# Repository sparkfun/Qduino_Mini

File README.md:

***NOTE:*** *This product was a Kickstarter product. If you are looking for more up-to-date info and the current version of this board, please check out the [current (Storefront) version](https://github.com/sparkfun/Qduino_Mini_SFE), [Qduino Mini product page](https://www.sparkfun.com/products/13614), or the [Arduino board support and library](https://github.com/sparkfun/Arduino_Boards).*

The Qduino Mini is *perfect* to embed in your electronics projects, it's super small, inexpensive, has a battery connector & charger built-in, & a fuel gauge that can tell you when to charge the battery!

The **Qduino Mini is Arduino-compatible & 100% open source, hardware and software** meaning that making and programming your first circuit is a breeze.  Hardware is hard, so we decided to make it a little bit easier.  All of the design files, including EAGLE board files, schematic, and code have been released under an open source license.  Here's what it includes:

* **Battery Charger Circuit** - just plug in USB and it charges the battery with the auto switching circuit - there's no extra charger needed & no digging the battery out of your project so you can charge & program at the same time over USB!
* **Battery Fuel Gauge** - guessing on when your project runs out of juice?  We've got you covered - we have a simple monitor library for your battery so you can remind yourself when it needs a little extra juice.
* **Ultra small, Ultra thin, Ultra light** - The Qduino Mini itself is 0.8in x 1.5in (2cm x 3.9cm) & 0.18oz (5 grams), perfect for quadcopters, drones or high altitude balloon projects.  Both the Qduino Mini and the batteries (LiPos) used to power the board fit are super compact & thin, just right for embedding in your projects.

######Tech Specs:

* **ATmega32U4 Processor** - Arduino Leonardo Compatible
* 32KB Flash Storage
* 2.5KB SRAM
* 1KB EEPROM
* 3.3V @ 8MHz
* 20 Digital I/O // 14 Dedicated
* 12 Analog Channels // 6 Dedicated
* 7 Digital I/O also PWM channels
* SPI, I2C, UART available
* Two RGB LEDs built-in - one for: Charge Status, TX, RX, and the * other user programmable
* **TPS78233** 3.3V 150mA Regulator
* **MCP73832** LiPo Battery Charger
* **MAX17048** LiPo Battery Fuel Gauge

The Qduino Mini is 100% made in the USA! Every board is made and quality tested at SparkFun Electronics, in Niwot, CO.

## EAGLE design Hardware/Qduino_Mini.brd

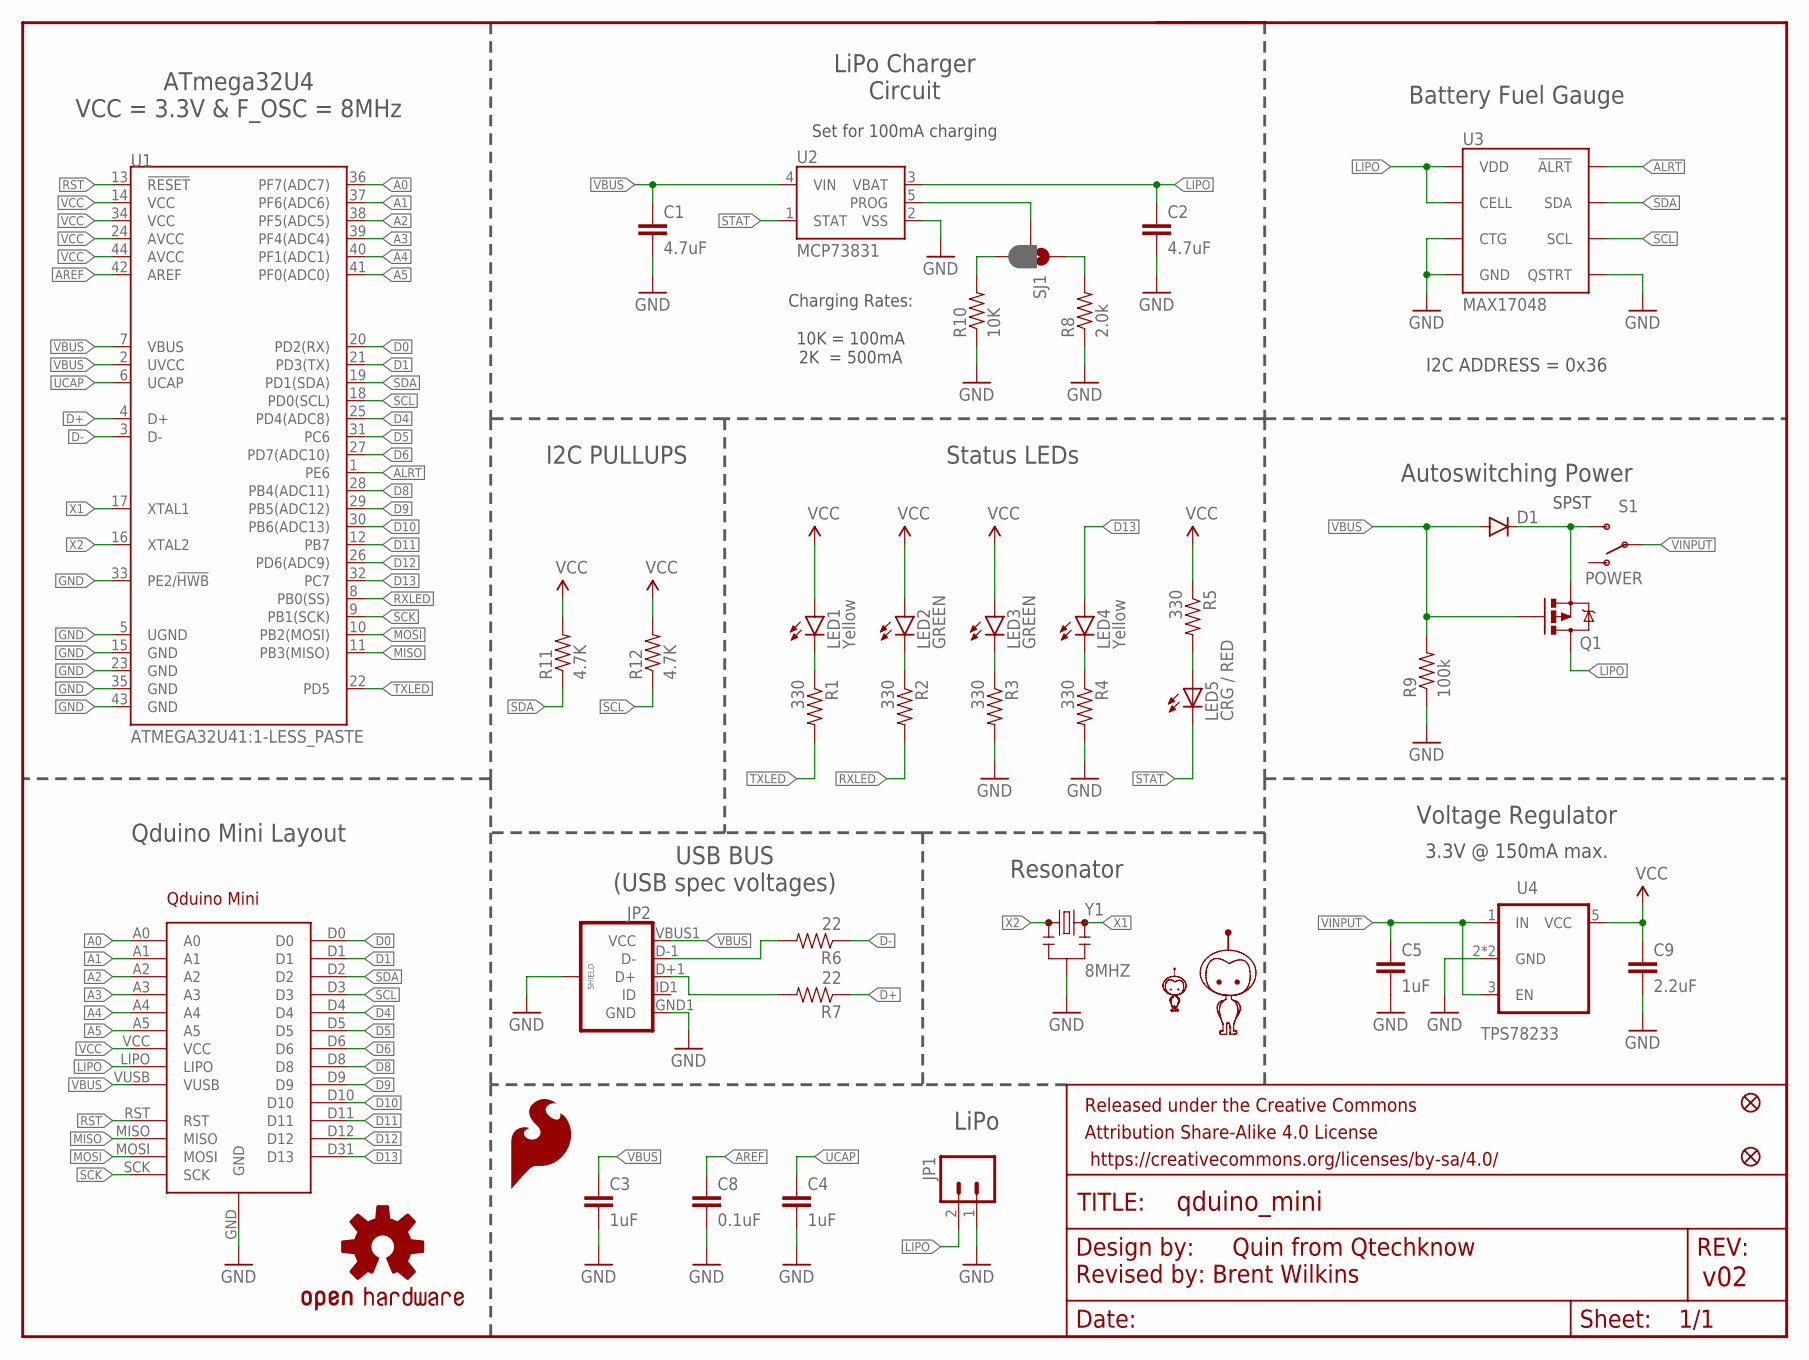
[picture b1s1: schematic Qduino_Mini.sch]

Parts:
C1, C2: 4.7uF; 0603-CAP
C3, C4, C5: 1uF; 0603-CAP
C8: 0.1uF; 0603-CAP
C9: 2.2uF; 0603-CAP
D1: 250mA/100V; SOD-323
FID5, FID6: FIDUCIAL1X2; FIDUCIAL-1X2
FRAME2: FRAME-LETTER; CREATIVE_COMMONS
JP1: LiPo; JST-2-SMD
JP2: USB_MICROB_PLUGCONN-11752; USB-B-MICRO-SMD_V03
LED1, LED4: Yellow; LED-0603
LED2, LED3: GREEN; LED-0603
LED5: CRG / RED; LED-0603
LOGO1: OSHW-LOGOS; OSHW-LOGO-S
LOGO2: SFE_LOGO_FLAME.1_INCH; SFE_LOGO_FLAME_.1
Q1: PFET; SOT23-3
R1, R2, R3, R4, R5: 330; 0603-RES
R6, R7: 22; 0603-RES
R8: 2.0k; 0603-RES
R9: 100k; 0603-RES
R10: 10K; 0603-RES
R11, R12: 4.7K; 0603-RES
S1: POWER; SWITCH-SPST-SMD-A
SJ1: JUMPER-PAD-3-2OF3_NC_BY_PASTE; PAD-JUMPER-3-2OF3_NC_BY_PASTE_YES_SILK_FULL_BOX
U1: ATMEGA32U41:1-LESS_PASTE; QFN-44-NOPAD_1:1-LESS_PASTE
U2: MCP73831; SOT23-5
U3: MAX17048; DFN-8
U4: TPS78233; SOT23-5
U5: MIGHTYQ-L-SILK; LOGO-LARGE-SILK
U6: MIGHTYQ-S-SILK; LOGO-SMALL-SILK
U7: DNP; QDUINO_MINI_V15
Y1: 8MHZ; RESONATOR-SMD

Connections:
A0: U1.36 (PF7(ADC7)), U7.A0
A1: U1.37 (PF6(ADC6)), U7.A1
A2: U1.38 (PF5(ADC5)), U7.A2
A3: U1.39 (PF4(ADC4)), U7.A3
A4: U1.40 (PF1(ADC1)), U7.A4
A5: U1.41 (PF0(ADC0)), U7.A5
ALRT: U1.1 (PE6), U3.P$5 (!ALRT)
AREF: C8.1, U1.42 (AREF)
D0: U1.20 (PD2(RX)), U7.D0
D1: U1.21 (PD3(TX)), U7.D1
D4: U1.25 (PD4(ADC8)), U7.D4
D5: U1.31 (PC6), U7.D5
D6: U1.27 (PD7(ADC10)), U7.D6
D8: U1.28 (PB4(ADC11)), U7.D8
D9: U1.29 (PB5(ADC12)), U7.D9
D10: U1.30 (PB6(ADC13)), U7.D10
D11: U1.12 (PB7), U7.D11
D12: U1.26 (PD6(ADC9)), U7.D12
D13: LED4.A, U1.32 (PC7), U7.D31 (D13)
D+: R7.1, U1.4 (D+)
D-: R6.1, U1.3 (D-)
GND: C1.2, C2.2, C3.2, C4.2, C5.2, C8.2, C9.2, JP1.1, JP2.GND1 (GND), JP2.SHIELD1 (SHIELD), JP2.SHIELD2 (SHIELD), JP2.SHIELD3 (SHIELD), R3.2, R4.2, R8.1, R9.1, R10.1, U1.5 (UGND), U1.15 (GND), U1.23 (GND), U1.33 (PE2/!HWB), U1.35 (GND), U1.43 (GND), U2.2 (VSS), U3.P$1 (CTG), U3.P$4 (GND), U3.P$6 (QSTRT), U3.P$9 (GND), U4.2 (GND), U4.4 (GND), U7.GND, Y1.2
INMOSFET: D1.C, Q1.2 (S), S1.3 (S)
LIPO: C2.1, JP1.2, Q1.3 (D), U2.3 (VBAT), U3.P$2 (CELL), U3.P$3 (VDD), U7.LIPO
MISO: U1.11 (PB3(MISO)), U7.MISO
MOSI: U1.10 (PB2(MOSI)), U7.MOSI
unnamed: LED1.C, R1.1
unnamed: LED2.C, R2.1
unnamed: LED5.A, R5.2
unnamed: LED4.C, R4.1
unnamed: R10.2, SJ1.3
unnamed: R8.2, SJ1.1
unnamed: LED3.C, R3.1
PROG: SJ1.2, U2.5 (PROG)
RST: U1.13 (!RESET), U7.RST
RXLED: R2.2, U1.8 (PB0(SS))
SCK: U1.9 (PB1(SCK)), U7.SCK
SCL: R12.1, U1.18 (PD0(SCL)), U3.P$7 (SCL), U7.D3
SDA: R11.1, U1.19 (PD1(SDA)), U3.P$8 (SDA), U7.D2
STAT: LED5.C, U2.1 (STAT)
TXLED: R1.2, U1.22 (PD5)
UCAP: C4.1, U1.6 (UCAP)
UD+: JP2.D+1 (D+), R7.2
UD-: JP2.D-1 (D-), R6.2
VBUS: C1.1, C3.1, D1.A, JP2.VBUS1 (VCC), Q1.1 (G), R9.2, U1.2 (UVCC), U1.7 (VBUS), U2.4 (VIN), U7.VUSB
VCC: C9.1, LED1.A, LED2.A, LED3.A, R5.1, R11.2, R12.2, U1.14 (VCC), U1.24 (AVCC), U1.34 (VCC), U1.44 (AVCC), U4.5 (VCC), U7.VCC
VINPUT: C5.1, S1.2, U4.1 (IN), U4.3 (EN)
X1: U1.17 (XTAL1), Y1.3
X2: U1.16 (XTAL2), Y1.1

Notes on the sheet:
Set for 100mA charging
USB BUS (USB spec voltages)
Resonator
Status LEDs
3.3V @ 150mA max.
SPST
ATmega32U4 VCC = 3.3V & F_OSC = 8MHz
Qduino Mini Layout
LiPo Charger Circuit
Battery Fuel Gauge
Voltage Regulator
Autoswitching Power
Charging Rates: 10K = 100mA 2K = 500mA
I2C PULLUPS
Revised by: Brent Wilkins
I2C ADDRESS = 0x36

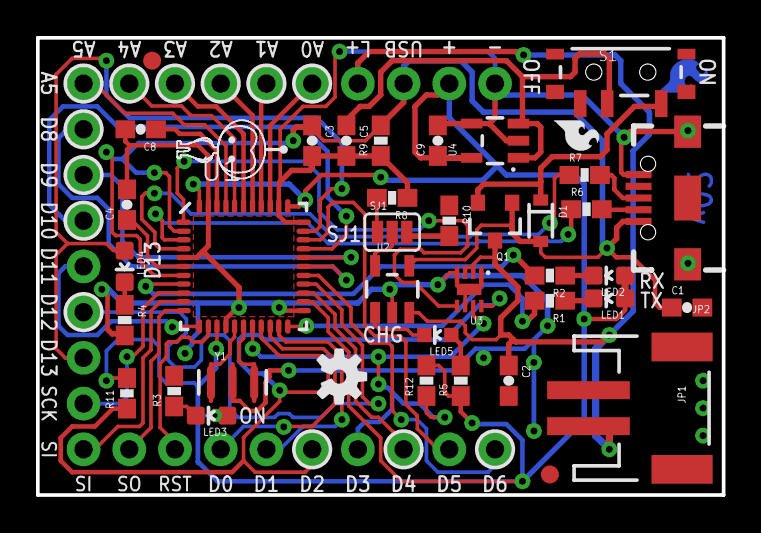
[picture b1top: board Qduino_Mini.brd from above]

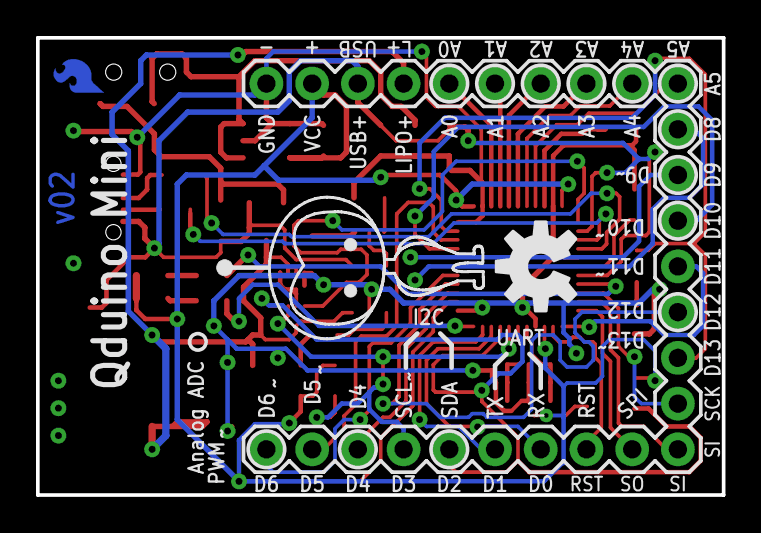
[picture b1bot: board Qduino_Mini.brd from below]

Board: 2 copper layers, 38.1 x 25.4 mm, 45 parts (3 on the bottom side), 49 nets.

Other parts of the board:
U$4: OSHW-LOGO-M
U$6: SFE-LOGO-FLAME-COPPER

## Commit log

2015-03-10 testing out a reduced sized die pad to provide the recommended mechanical support, but with low pad to pin short likelihood
2015-03-10 Rerouted grounds under IC
    Cleaned the ground traces under IC up. Passes DRC now too.
2015-03-10 Fixed a y junction
    being picky
2015-03-19 Used version of MCP73831 in current library, rather than legacy library. No real change.
2015-04-07 Updated capactior ID
2015-04-22 Moved battery over to make rework easier. In the process moved the power LED to the middle. Also fixed RX/TX lines(D0/D1)
2015-04-22 Incremented version #
2015-04-23 Added info on safe voltages & oscillator speeds
2015-04-24 Added I2C address to schematic for fuel gauge. No change to PCB
2015-05-18 Added 'IC-' prefix to the attriburtes of a part
2015-09-26 Added a pdf of the schematic
2015-09-30 Removed ISR from fuelGauge library
2015-09-30 Fixed lib in second place
2015-10-07 Reverted example that made function call to the ISR version
2015-12-22 Ignored table 28-3 in datasheet about the extended fuse bits. Changing bits 5:4 to 0's as a workaround to bug in AVRDUDE (https://savannah.nongnu.org/bugs/?21954).
2016-01-08 Added not to link to current version
2016-02-10 Expanded on license
2016-02-11 Update LICENSE.md
    Quin wrote the majority of the user facing code. Changing default license to give him credit.

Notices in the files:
parts and their libraries:
SparkFun-Passives: Licensing: CC v3.0 Share-Alike You are welcome to use this library for commercial purposes.
SparkFun-Aesthetics: Released under the Creative Commons Attribution Share-Alike 4.0 License
SparkFun-Aesthetics: https://creativecommons.org/licenses/by-sa/4.0
